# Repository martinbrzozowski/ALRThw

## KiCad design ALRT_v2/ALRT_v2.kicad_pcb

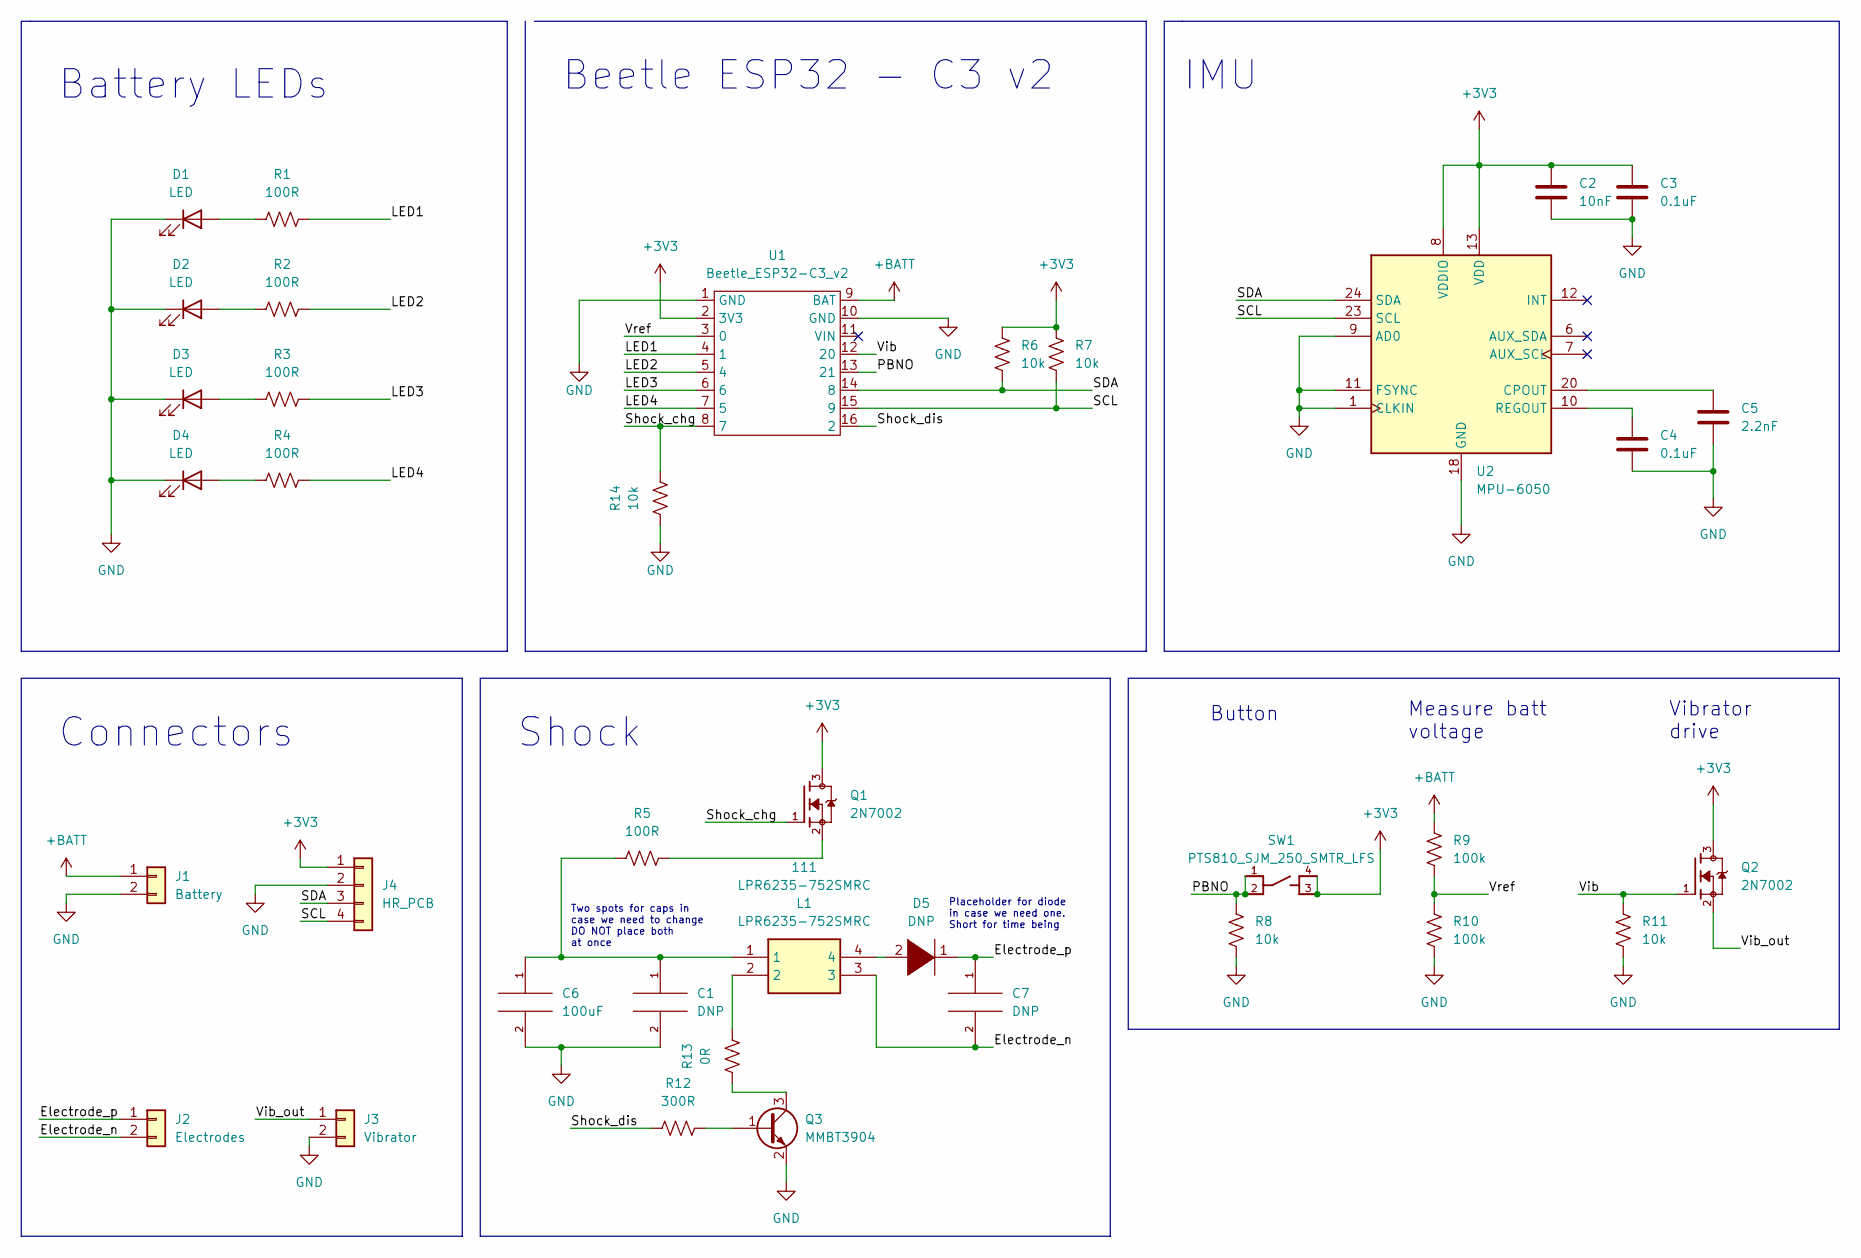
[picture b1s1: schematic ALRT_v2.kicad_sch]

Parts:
111: LPR6235-752SMRC; LPR6235_1; Mouser Part Number 994-LPR6235-752SMRC
C1: DNP; C_0805_2012Metric
C2: 10nF; C_0603_1608Metric
C3, C4: 0.1uF; C_0603_1608Metric
C5: 2.2nF; C_0603_1608Metric
C6: 100uF; C_1206_3216Metric
C7: DNP; C_0603_1608Metric
D1, D2, D3, D4: LED; LED_0603_1608Metric
D5: DNP; D_SOD-123
J1: Battery; PinHeader_1x02_P2.54mm_Vertical
J2: Electrodes; PinHeader_1x02_P2.54mm_Vertical
J3: Vibrator; PinHeader_1x02_P2.54mm_Vertical
J4: HR_PCB; PinHeader_1x04_P2.54mm_Vertical
Q1, Q2: 2N7002; SOT95P240X111-3N; PARTREV 4
Q3: MMBT3904; SOT-23
R1, R2, R3, R4, R5: 100R; R_0603_1608Metric
R6, R7, R8, R11, R14: 10k; R_0603_1608Metric
R9, R10: 100k; R_0603_1608Metric
R12: 300R; R_0603_1608Metric
R13: 0R; R_0603_1608Metric
SW1: PTS810_SJM_250_SMTR_LFS; SW_PTS810_SJM_250_SMTR_LFS
U1: Beetle_ESP32-C3_v2; Beetle_ESP32_C3
U2: MPU-6050; InvenSense_QFN-24_4x4mm_P0.5mm

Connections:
+3V3: C2.1, C3.1, J4.1, Q1.3, Q2.3, R6.2, R7.2, SW1.3, SW1.4, U1.2 (3V3), U2.8 (VDDIO), U2.13 (VDD)
+BATT: J1.1, R9.2, U1.9 (BAT)
/Electrode_n: 111.3, C7.2, J2.2; also elsewhere on the board
/Electrode_p: C7.1, D5.1 (A), J2.1
/LED1: R1.2, U1.4 (1)
/LED2: R2.2, U1.5 (4)
/LED3: R3.2, U1.6
/LED4: R4.2, U1.7 (5)
/PBNO: R8.2, SW1.1, SW1.2, U1.13 (21)
/SCL: J4.4, R7.1, U1.15 (9), U2.23 (SCL)
/SDA: J4.3, R6.1, U1.14 (8), U2.24 (SDA)
/Shock_chg: Q1.1, R14.1, U1.8 (7)
/Shock_dis: R12.2, U1.16 (2)
/Vib: Q2.1, R11.2, U1.12 (20)
/Vib_out: J3.1, Q2.2
/Vref: R9.1, R10.2, U1.3 (0)
GND: C1.2, C2.2, C3.2, C4.2, C5.2, C6.2, D1.1 (K), D2.1 (K), D3.1 (K), D4.1 (K), J1.2, J3.2, J4.2, Q3.2 (E), R8.1, R10.1, R11.1, R14.2, U1.1 (GND), U1.10 (GND), U2.1 (CLKIN), U2.9 (AD0), U2.11 (FSYNC), U2.18 (GND)
unnamed 17: 111.1, C1.1, C6.1, R5.2; also elsewhere on the board
unnamed: C4.1, U2.10 (REGOUT)
unnamed: C5.1, U2.20 (CPOUT)
unnamed: D1.2 (A), R1.1
unnamed: D2.2 (A), R2.1
unnamed: D3.2 (A), R3.1
unnamed: D4.2 (A), R4.1
unnamed 24: 111.4, D5.2 (K); also elsewhere on the board
unnamed: Q1.2, R5.1
unnamed: Q3.1 (B), R12.1
unnamed: Q3.3 (C), R13.2
unnamed 28: 111.2, R13.1; also elsewhere on the board

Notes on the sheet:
Two spots for caps in case we need to change DO NOT place both at once
Vibrator drive
Battery LEDs
Connectors
IMU
Measure batt voltage
Placeholder for diode in case we need one. Short for time being
Button
Shock
Beetle ESP32 - C3 v2

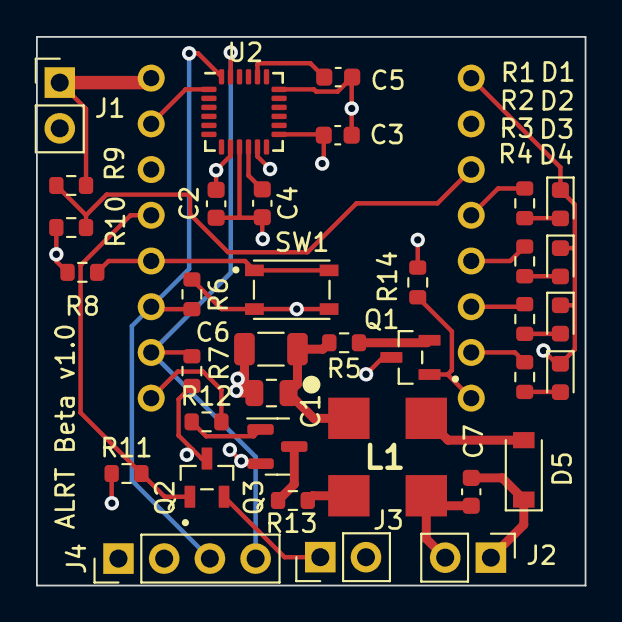
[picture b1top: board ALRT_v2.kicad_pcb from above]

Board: 4 copper layers, 30.5 x 30.5 mm, 37 parts (1 on the bottom side), 29 nets.

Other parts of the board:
L1: LPR6235-752SMRC; LPR6235_1

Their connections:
/Electrode_n: L1.3; also elsewhere on the board
unnamed 17: L1.1; also elsewhere on the board
unnamed 24: L1.4; also elsewhere on the board
unnamed 28: L1.2; also elsewhere on the board

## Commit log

2024-01-24 Add files via upload
    Added ALRT v1 kicad files. Copy the ALRT_v1 directory and paste it as ALRT_v2. The files are a little disorganized, and could use some cleaning up.
2024-02-05 initial copy of alrt v1 folder into v2
2024-02-05 started removing beetle board and reconfigured charge circuit
2024-03-31 initial daughterboard removal
